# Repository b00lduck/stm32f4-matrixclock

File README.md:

# stm32f4-matrixclock
Use the STM32F4 to drive a large LED matrix with TLC5940

### Port mapping:

 - PA8  GSCLK	common PWM-clock for the TLC5940s    (TIM1 AF1)

 - PC6  BLANK   common BLANK-signal for the TLC5940s (TIM3 AF2)
 - PC7  LATCH   common LATCH-signal for the TLC5940s (TIM3 AF2)
 - PC9  SCK     common LATCH-signal for the TLC5940s (TIM8 AF3)

 - PD12 LED4	discovery board
 - PD13 LED3	discovery board
 - PD14 LED5	discovery board
 - PD15 LED6  	discovery board

 - PE0  SDA_A	Sector A data (DMA)
 - PE1  SDA_B	Sector B data (DMA)
 - PE2  SDA_C	Sector C data (DMA)
 - PE3  SDA_D	Sector D data (DMA)
 - PE4  SDA_E	Sector E data (DMA)
 - PE5  SDA_F	Sector F data (DMA)
 - PE6  SDA_G	Sector G data (DMA)
 - PE7  SDA_H	Sector H data (DMA)

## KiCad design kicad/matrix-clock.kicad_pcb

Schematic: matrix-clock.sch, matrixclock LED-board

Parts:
C2: 100uF; C_Radial_D10_L20_P5
C3, C4, C5, C6, C7, C8, C9, C10: 100n; C_Disc_D3_P2.5
D1, D2, D3, D4, D5, D6, D7, D8, D9, D10, D11, D12, D13, D14, D15, D16, D17, D18, D19, D20, D21, D22, D23, D24, D25, D26, D27, D28, D29, D30, D31, D32, D33, D34, D35, D36, D37, D38, D39, D40, D41, D42, D43, D44, D45, D46, D47, D48, D49, D50, D51, D52, D53, D54, D55, D56, D57, D58, D59, D60, D61, D62, D63, D64, D65, D66, D67, D68, D69, D70, D71, D72, D73, D74, D75, D76, D77, D78, D79, D80, D81, D82, D83, D84, D85, D86, D87, D88, D89, D90, D91, D92, D93, D94, D95, D96, D97, D98, D99, D100, D101, D102, D103, D104, D105, D106, D107, D108, D109, D110, D111, D112, D113, D114, D115, D116, D117, D118, D119, D120, D121, D122, D123, D124, D125, D126, D127, D128: LED; MENTOR 50.046
P1: CONN_02X08; Pin_Header_Straight_2x08
P3: CONN_01X02; Pin_Header_Straight_1x02
R1, R2, R3, R4, R5, R6, R7, R8: 2k; Resistor_Horizontal_RM7mm
TLC1, TLC2, TLC3, TLC4, TLC5, TLC6, TLC7, TLC8: TLC5940; DIP-28_W7.62mm

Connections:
/BLANK: P1.8, TLC1.23 (BLANK), TLC2.23 (BLANK), TLC3.23 (BLANK), TLC4.23 (BLANK), TLC5.23 (BLANK), TLC6.23 (BLANK), TLC7.23 (BLANK), TLC8.23 (BLANK)
/DCPRG: P1.6, TLC1.19 (DCPRG), TLC2.19 (DCPRG), TLC3.19 (DCPRG), TLC4.19 (DCPRG), TLC5.19 (DCPRG), TLC6.19 (DCPRG), TLC7.19 (DCPRG), TLC8.19 (DCPRG)
/GSCLK: P1.4, TLC1.18 (GSCLK), TLC2.18 (GSCLK), TLC3.18 (GSCLK), TLC4.18 (GSCLK), TLC5.18 (GSCLK), TLC6.18 (GSCLK), TLC7.18 (GSCLK), TLC8.18 (GSCLK)
/SCLK: P1.12, TLC1.25 (SCLK), TLC2.25 (SCLK), TLC3.25 (SCLK), TLC4.25 (SCLK), TLC5.25 (SCLK), TLC6.25 (SCLK), TLC7.25 (SCLK), TLC8.25 (SCLK)
/VPRG: P1.16, TLC1.27 (VPRG), TLC2.27 (VPRG), TLC3.27 (VPRG), TLC4.27 (VPRG), TLC5.27 (VPRG), TLC6.27 (VPRG), TLC7.27 (VPRG), TLC8.27 (VPRG)
/XLAT: P1.10, TLC1.24 (XLAT), TLC2.24 (XLAT), TLC3.24 (XLAT), TLC4.24 (XLAT), TLC5.24 (XLAT), TLC6.24 (XLAT), TLC7.24 (XLAT), TLC8.24 (XLAT)
GND: C2.2, C3.2, C4.2, C5.2, C6.2, C7.2, C8.2, C9.2, C10.2, P1.1, P1.3, P1.5, P1.7, P1.9, P1.11, P1.13, P1.15, R1.1, R2.1, R3.1, R4.1, R5.1, R6.1, R7.1, R8.1, TLC1.22 (GND), TLC2.22 (GND), TLC3.22 (GND), TLC4.22 (GND), TLC5.22 (GND), TLC6.22 (GND), TLC7.22 (GND), TLC8.22 (GND); also elsewhere on the board
unnamed: D1.1 (K), TLC1.28 (OUT$0)
unnamed: D2.1 (K), TLC1.1 (OUT$1)
unnamed: D3.1 (K), TLC1.2 (OUT$2)
unnamed: D4.1 (K), TLC1.3 (OUT$3)
unnamed: D5.1 (K), TLC1.4 (OUT$4)
unnamed: D6.1 (K), TLC1.5 (OUT$5)
unnamed: D7.1 (K), TLC1.6 (OUT$6)
unnamed: D8.1 (K), TLC1.7 (OUT$7)
unnamed: D9.1 (K), TLC1.8 (OUT$8)
unnamed: D10.1 (K), TLC1.9 (OUT$9)
unnamed: D11.1 (K), TLC1.10 (OUT$10)
unnamed: D12.1 (K), TLC1.11 (OUT$11)
unnamed: D13.1 (K), TLC1.12 (OUT$12)
unnamed: D14.1 (K), TLC1.13 (OUT$13)
unnamed: D15.1 (K), TLC1.14 (OUT$14)
unnamed: D16.1 (K), TLC1.15 (OUT$15)
unnamed: D17.1 (K), TLC2.28 (OUT$0)
unnamed: D18.1 (K), TLC2.1 (OUT$1)
unnamed: D19.1 (K), TLC2.2 (OUT$2)
unnamed: D20.1 (K), TLC2.3 (OUT$3)
unnamed: D21.1 (K), TLC2.4 (OUT$4)
unnamed: D22.1 (K), TLC2.5 (OUT$5)
unnamed: D23.1 (K), TLC2.6 (OUT$6)
unnamed: D24.1 (K), TLC2.7 (OUT$7)
unnamed: D25.1 (K), TLC2.8 (OUT$8)
unnamed: D26.1 (K), TLC2.9 (OUT$9)
unnamed: D27.1 (K), TLC2.10 (OUT$10)
unnamed: D28.1 (K), TLC2.11 (OUT$11)
unnamed: D29.1 (K), TLC2.12 (OUT$12)
unnamed: D30.1 (K), TLC2.13 (OUT$13)
unnamed: D31.1 (K), TLC2.14 (OUT$14)
unnamed: D32.1 (K), TLC2.15 (OUT$15)
unnamed: D33.1 (K), TLC3.28 (OUT$0)
unnamed: D34.1 (K), TLC3.1 (OUT$1)
unnamed: D35.1 (K), TLC3.2 (OUT$2)
unnamed: D36.1 (K), TLC3.3 (OUT$3)
unnamed: D37.1 (K), TLC3.4 (OUT$4)
unnamed: D38.1 (K), TLC3.5 (OUT$5)
unnamed: D39.1 (K), TLC3.6 (OUT$6)
unnamed: D40.1 (K), TLC3.7 (OUT$7)
unnamed: D41.1 (K), TLC3.8 (OUT$8)
unnamed: D42.1 (K), TLC3.9 (OUT$9)
unnamed: D43.1 (K), TLC3.10 (OUT$10)
unnamed: D44.1 (K), TLC3.11 (OUT$11)
unnamed: D45.1 (K), TLC3.12 (OUT$12)
unnamed: D46.1 (K), TLC3.13 (OUT$13)
unnamed: D47.1 (K), TLC3.14 (OUT$14)
unnamed: D48.1 (K), TLC3.15 (OUT$15)
unnamed: D49.1 (K), TLC4.28 (OUT$0)
unnamed: D50.1 (K), TLC4.1 (OUT$1)
unnamed: D51.1 (K), TLC4.2 (OUT$2)
unnamed: D52.1 (K), TLC4.3 (OUT$3)
unnamed: D53.1 (K), TLC4.4 (OUT$4)
unnamed: D54.1 (K), TLC4.5 (OUT$5)
unnamed: D55.1 (K), TLC4.6 (OUT$6)
unnamed: D56.1 (K), TLC4.7 (OUT$7)
unnamed: D57.1 (K), TLC4.8 (OUT$8)
unnamed: D58.1 (K), TLC4.9 (OUT$9)
unnamed: D59.1 (K), TLC4.10 (OUT$10)
unnamed: D60.1 (K), TLC4.11 (OUT$11)
unnamed: D61.1 (K), TLC4.12 (OUT$12)
unnamed: D62.1 (K), TLC4.13 (OUT$13)
unnamed: D63.1 (K), TLC4.14 (OUT$14)
unnamed: D64.1 (K), TLC4.15 (OUT$15)
unnamed: D65.1 (K), TLC5.28 (OUT$0)
unnamed: D66.1 (K), TLC5.1 (OUT$1)
unnamed: D67.1 (K), TLC5.2 (OUT$2)
unnamed: D68.1 (K), TLC5.3 (OUT$3)
unnamed: D69.1 (K), TLC5.4 (OUT$4)
unnamed: D70.1 (K), TLC5.5 (OUT$5)
unnamed: D71.1 (K), TLC5.6 (OUT$6)
unnamed: D72.1 (K), TLC5.7 (OUT$7)
unnamed: D73.1 (K), TLC5.8 (OUT$8)
unnamed: D74.1 (K), TLC5.9 (OUT$9)
unnamed: D75.1 (K), TLC5.10 (OUT$10)
unnamed: D76.1 (K), TLC5.11 (OUT$11)
unnamed: D77.1 (K), TLC5.12 (OUT$12)
unnamed: D78.1 (K), TLC5.13 (OUT$13)
unnamed: D79.1 (K), TLC5.14 (OUT$14)
unnamed: D80.1 (K), TLC5.15 (OUT$15)
unnamed: D81.1 (K), TLC6.28 (OUT$0)
unnamed: D82.1 (K), TLC6.1 (OUT$1)
unnamed: D83.1 (K), TLC6.2 (OUT$2)
unnamed: D84.1 (K), TLC6.3 (OUT$3)
unnamed: D85.1 (K), TLC6.4 (OUT$4)
unnamed: D86.1 (K), TLC6.5 (OUT$5)
unnamed: D87.1 (K), TLC6.6 (OUT$6)
unnamed: D88.1 (K), TLC6.7 (OUT$7)
unnamed: D89.1 (K), TLC6.8 (OUT$8)
unnamed: D90.1 (K), TLC6.9 (OUT$9)
unnamed: D91.1 (K), TLC6.10 (OUT$10)
unnamed: D92.1 (K), TLC6.11 (OUT$11)
unnamed: D93.1 (K), TLC6.12 (OUT$12)
unnamed: D94.1 (K), TLC6.13 (OUT$13)
unnamed: D95.1 (K), TLC6.14 (OUT$14)
unnamed: D96.1 (K), TLC6.15 (OUT$15)
unnamed: D97.1 (K), TLC7.28 (OUT$0)
unnamed: D98.1 (K), TLC7.1 (OUT$1)
unnamed: D99.1 (K), TLC7.2 (OUT$2)
unnamed: D100.1 (K), TLC7.3 (OUT$3)
unnamed: D101.1 (K), TLC7.4 (OUT$4)
unnamed: D102.1 (K), TLC7.5 (OUT$5)
unnamed: D103.1 (K), TLC7.6 (OUT$6)
unnamed: D104.1 (K), TLC7.7 (OUT$7)
unnamed: D105.1 (K), TLC7.8 (OUT$8)
unnamed: D106.1 (K), TLC7.9 (OUT$9)
unnamed: D107.1 (K), TLC7.10 (OUT$10)
unnamed: D108.1 (K), TLC7.11 (OUT$11)
unnamed: D109.1 (K), TLC7.12 (OUT$12)
unnamed: D110.1 (K), TLC7.13 (OUT$13)
unnamed: D111.1 (K), TLC7.14 (OUT$14)
unnamed: D112.1 (K), TLC7.15 (OUT$15)
unnamed: D113.1 (K), TLC8.28 (OUT$0)
unnamed: D114.1 (K), TLC8.1 (OUT$1)
unnamed: D115.1 (K), TLC8.2 (OUT$2)
unnamed: D116.1 (K), TLC8.3 (OUT$3)
unnamed: D117.1 (K), TLC8.4 (OUT$4)
unnamed: D118.1 (K), TLC8.5 (OUT$5)
unnamed: D119.1 (K), TLC8.6 (OUT$6)
unnamed: D120.1 (K), TLC8.7 (OUT$7)
unnamed: D121.1 (K), TLC8.8 (OUT$8)
unnamed: D122.1 (K), TLC8.9 (OUT$9)
unnamed: D123.1 (K), TLC8.10 (OUT$10)
unnamed: D124.1 (K), TLC8.11 (OUT$11)
unnamed: D125.1 (K), TLC8.12 (OUT$12)
unnamed: D126.1 (K), TLC8.13 (OUT$13)
unnamed: D127.1 (K), TLC8.14 (OUT$14)
unnamed: D128.1 (K), TLC8.15 (OUT$15)
unnamed: P1.14, TLC1.26 (SIN)
unnamed: R1.2, TLC1.20 (IREF)
unnamed: R2.2, TLC2.20 (IREF)
unnamed: R3.2, TLC3.20 (IREF)
unnamed: R4.2, TLC4.20 (IREF)
unnamed: R5.2, TLC5.20 (IREF)
unnamed: R6.2, TLC6.20 (IREF)
unnamed: R7.2, TLC7.20 (IREF)
unnamed: R8.2, TLC8.20 (IREF)
unnamed: TLC1.17 (SOUT), TLC2.26 (SIN)
unnamed: TLC2.17 (SOUT), TLC3.26 (SIN)
unnamed: TLC3.17 (SOUT), TLC4.26 (SIN)
unnamed: TLC4.17 (SOUT), TLC5.26 (SIN)
unnamed: TLC5.17 (SOUT), TLC6.26 (SIN)
unnamed: TLC6.17 (SOUT), TLC7.26 (SIN)
unnamed: TLC7.17 (SOUT), TLC8.26 (SIN)

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
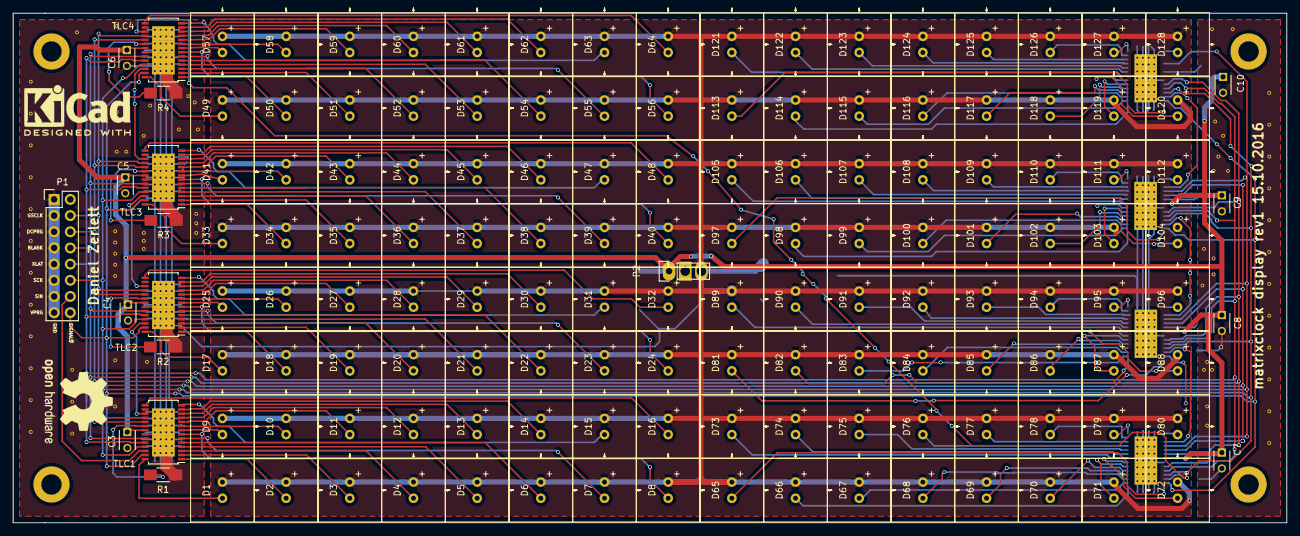
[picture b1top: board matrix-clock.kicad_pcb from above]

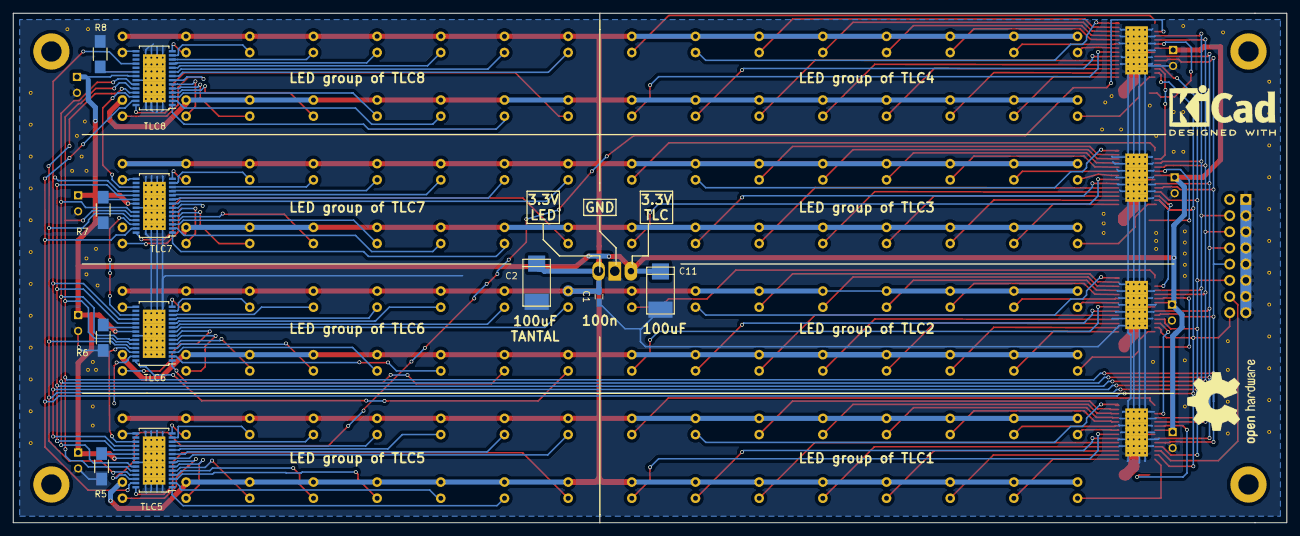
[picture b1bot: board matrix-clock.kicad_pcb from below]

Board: 2 copper layers, 200.0 x 80.0 mm, 157 parts (11 on the bottom side), 153 nets.

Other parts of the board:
C1: 100n; C_0603_HandSoldering
C11: 100uF; TantalC_SizeX_EIA-7343
P2: Pin_Header_Straight_1x03_fett

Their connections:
GND: C1.2, C11.2, P2.2; also elsewhere on the board

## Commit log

2016-10-06 changed license
2016-10-07 gitignore
2016-10-07 BLANK signal generation via TIM1 72Hz
2016-10-07 free running TIM3 for GSCLK
2016-10-07 free running TIM3
2016-10-08 Complete GSCLK/BLANK signal generation
2016-10-08 tighten timing
2016-10-08 LATCH signal
2016-10-08 Added port mappings to README
2016-10-08 Data signal triggered
2016-10-08 DMA output
2016-10-10 added schematics and board for display
2016-10-10 first test gradient
2016-10-11 8x16 matrix test
2016-10-14 board layout
2016-10-14 layout changes
2016-10-15 finalized board
2016-10-15 moved gerber files
2016-10-15 added gerber
2016-10-15 production files
2016-10-17 removed lib
2016-10-19 removed libs
2016-10-19 pcb fixes
2016-10-22 modified board
